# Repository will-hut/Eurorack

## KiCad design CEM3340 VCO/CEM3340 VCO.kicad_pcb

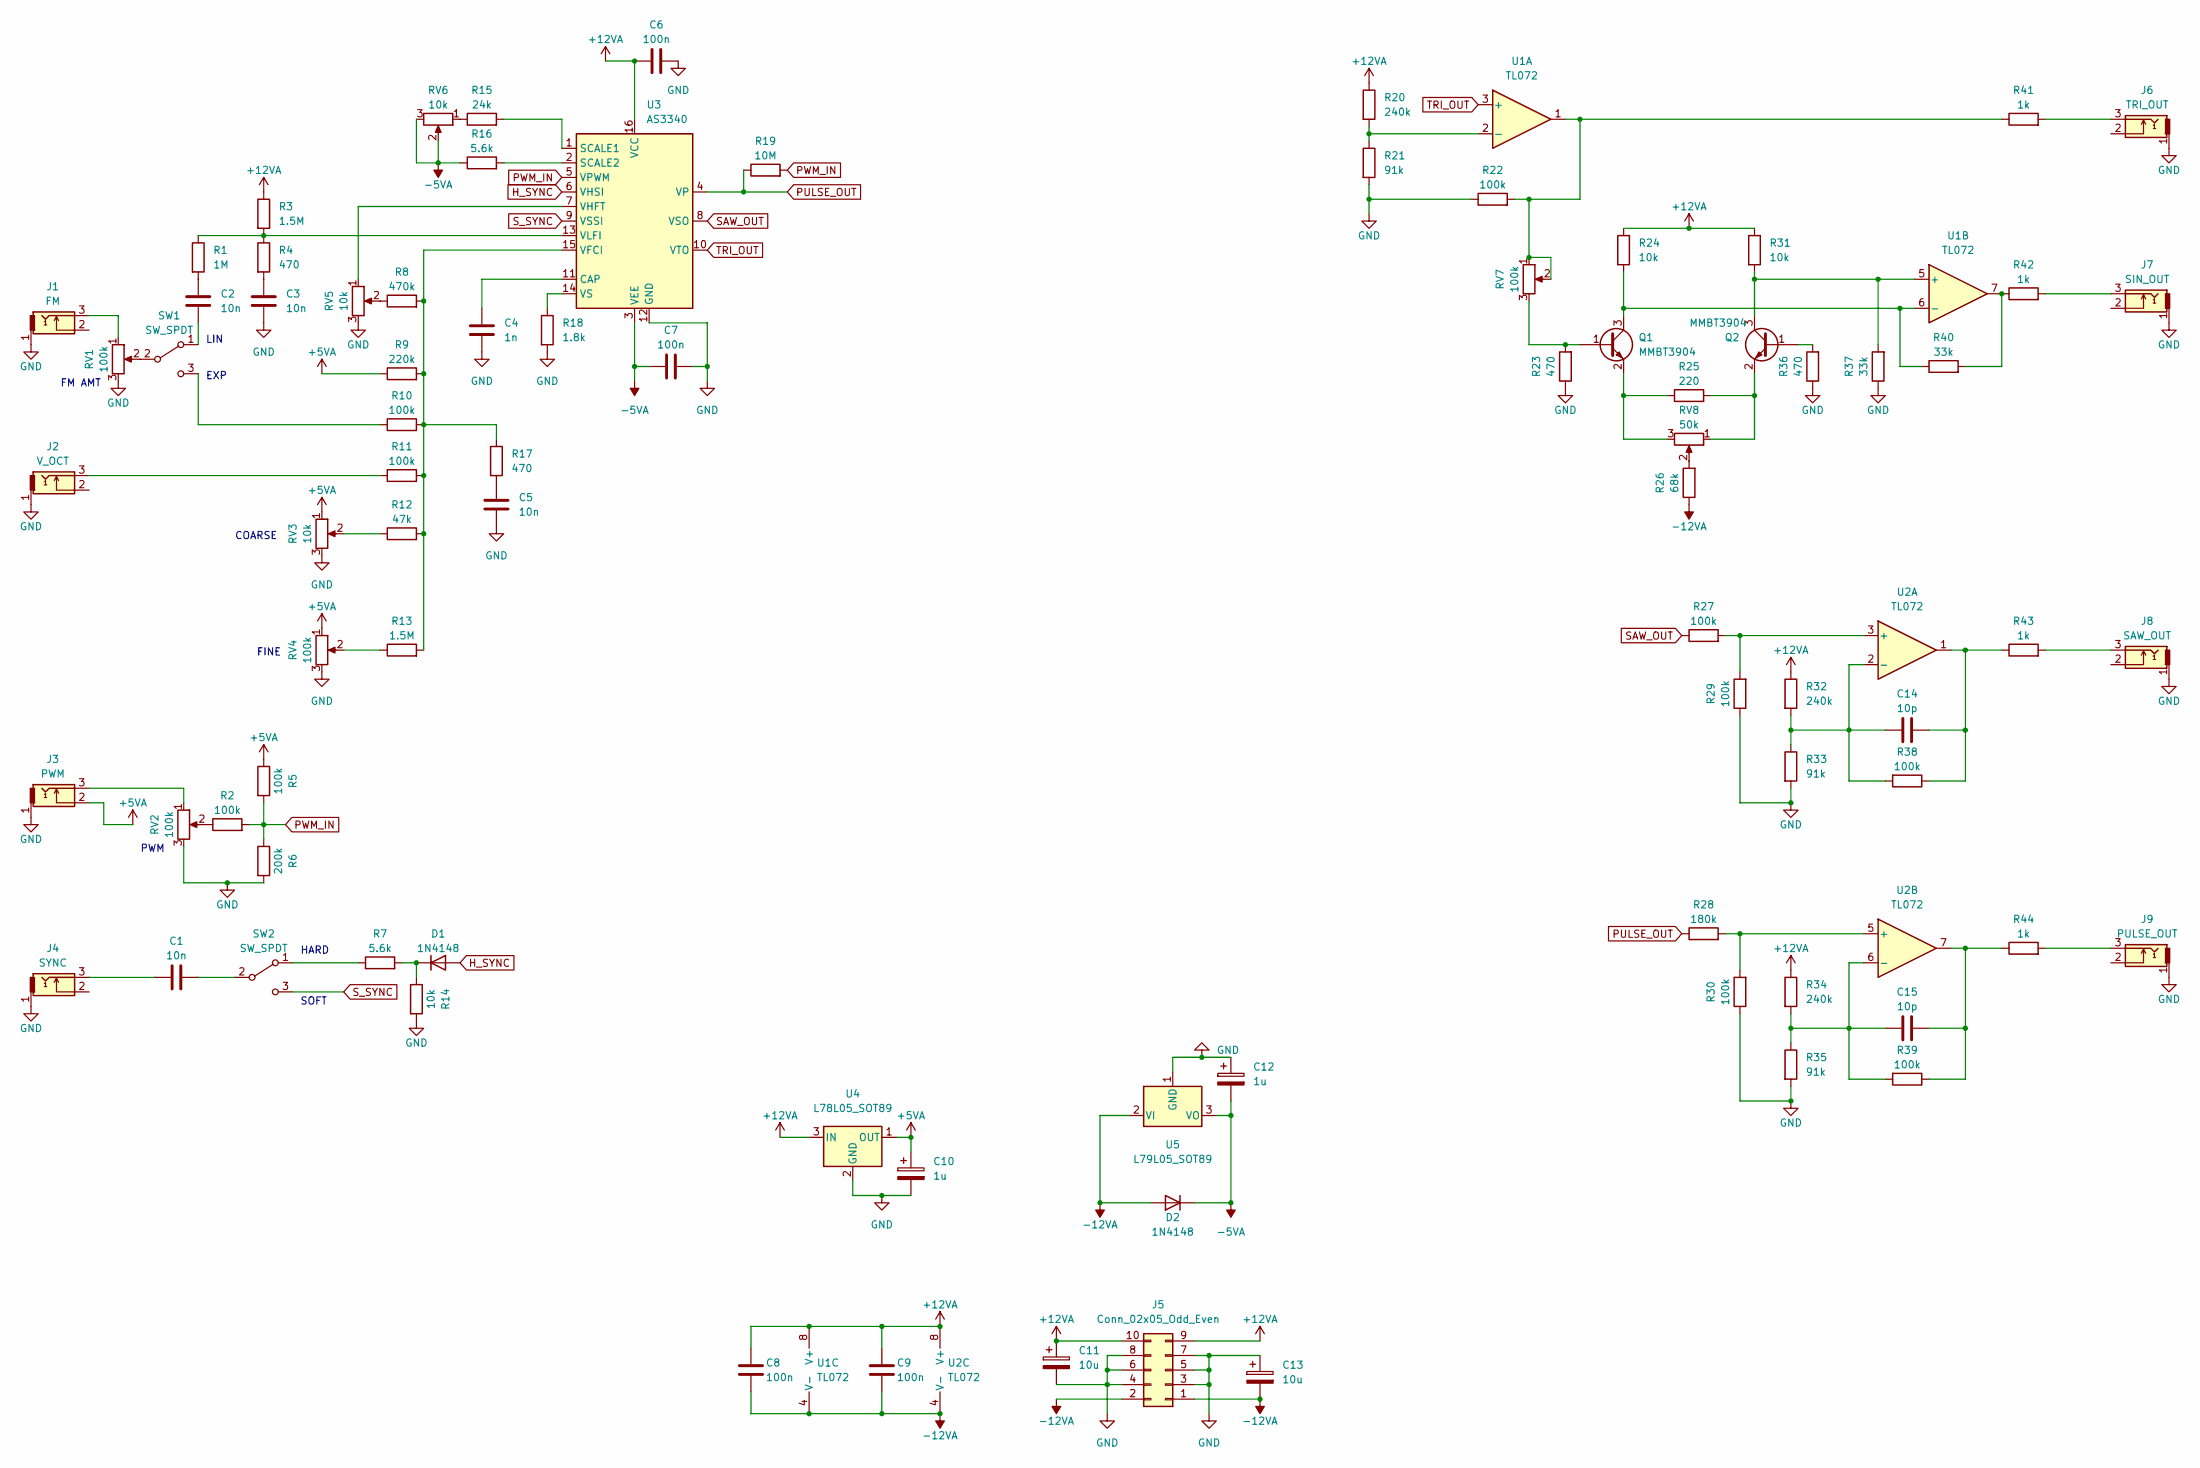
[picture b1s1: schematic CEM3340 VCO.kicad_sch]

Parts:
C1, C2, C3, C5: 10n; C_0603_1608Metric; LCSC C57112
C4: 1n; C_0603_1608Metric; LCSC C77026
C6, C7, C8, C9: 100n; C_0603_1608Metric; LCSC C14663
C10, C12: 1u; C_0603_1608Metric; LCSC C15849
C11, C13: 10u; CP_Radial_D6.3mm_P2.50mm
C14, C15: 10p; C_0603_1608Metric; LCSC C1634
D1, D2: 1N4148; D_SOD-123; LCSC C2128
J1: FM; thonkiconn
J2: V_OCT; thonkiconn
J3: PWM; thonkiconn
J4: SYNC; thonkiconn
J5: Conn_02x05_Odd_Even; PinHeader_2x05_P2.54mm_Vertical
J6: TRI_OUT; thonkiconn
J7: SIN_OUT; thonkiconn
J8: SAW_OUT; thonkiconn
J9: PULSE_OUT; thonkiconn
Q1, Q2: MMBT3904; SOT-23; LCSC C20526
R1: 1M; R_0603_1608Metric; LCSC C22935
R2, R5, R10, R11, R22, R27, R29, R30, R38, R39: 100k; R_0603_1608Metric; LCSC C25803
R3, R13: 1.5M; R_0603_1608Metric; LCSC C4172
R4, R17, R23, R36: 470; R_0603_1608Metric; LCSC C23179
R6: 200k; R_0603_1608Metric; LCSC C25811
R7, R16: 5.6k; R_0603_1608Metric; LCSC C23189
R8: 470k; R_0603_1608Metric; LCSC C23178
R9: 220k; R_0603_1608Metric; LCSC C22961
R12: 47k; R_0603_1608Metric; LCSC C25819
R14, R24, R31: 10k; R_0603_1608Metric; LCSC C25804
R15: 24k; R_0603_1608Metric; LCSC C23352
R18: 1.8k; R_0603_1608Metric; LCSC C4177
R19: 10M; R_0603_1608Metric; LCSC C7250
R20, R32, R34: 240k; R_0603_1608Metric; LCSC C4197
R21, R33, R35: 91k; R_0603_1608Metric; LCSC C23265
R25: 220; R_0603_1608Metric; LCSC C22962
R26: 68k; R_0603_1608Metric; LCSC C23231
R28: 180k; R_0603_1608Metric; LCSC C22827
R37, R40: 33k; R_0603_1608Metric; LCSC C4216
R41, R42, R43, R44: 1k; R_0603_1608Metric; LCSC C21190
RV1, RV2, RV4: 100k; alpha_rd901f
RV3: 10k; alpha_rd901f
RV5, RV6: 10k; Potentiometer_Bourns_3296W_Vertical
RV7: 100k; Potentiometer_Bourns_3296W_Vertical
RV8: 50k; Potentiometer_Bourns_3296W_Vertical
SW1, SW2: SW_SPDT; sw_dailywell_2M_M2
U1, U2: TL072; SOIC-8_3.9x4.9mm_P1.27mm; LCSC C6961
U3: AS3340; SO-16_3.9x9.9mm_P1.27mm
U4: L78L05_SOT89; SOT-89-3; LCSC C71136
U5: L79L05_SOT89; SOT-89-3; LCSC C157452

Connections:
+5VA: C10.1, J3.2, R5.1, R9.1, RV3.1, RV4.1, U4.1 (OUT)
+12VA: C6.1, C8.1, C9.1, C11.1, J5.9, J5.10, R3.1, R20.1, R24.1, R31.1, R32.1, R34.1, U1.8 (V+), U2.8 (V+), U3.16 (VCC), U4.3 (IN)
-5VA: C7.1, C12.2, D2.1 (K), R16.1, RV6.2, RV6.3, U3.3 (VEE), U5.3 (VO)
-12VA: C8.2, C9.2, C13.2, D2.2 (A), J5.1, J5.2, R26.1, U1.4 (V-), U2.4 (V-), U5.2 (VI)
GND: C3.2, C4.2, C5.2, C6.2, C7.2, C10.2, C11.2, C12.1, C13.1, J1.1, J2.1, J3.1, J4.1, J5.3, J5.4, J5.5, J5.6, J5.7, J5.8, J6.1, J7.1, J8.1, J9.1, R6.2, R14.2, R18.2, R21.2, R22.1, R23.1, R29.1, R30.1, R33.2, R35.2, R36.1, R37.1, RV1.3, RV2.3, RV3.3, RV4.3, RV5.3, U3.12 (GND), U4.2 (GND), U5.1 (GND)
H_SYNC: D1.2 (A), U3.6 (VHSI)
unnamed: C1.1, J4.3
unnamed: C1.2, SW2.2 (B)
unnamed: C2.1, R1.2
unnamed: C2.2, SW1.1 (A)
unnamed: C3.1, R4.2
unnamed: C4.1, U3.11 (CAP)
unnamed: C5.1, R17.2
unnamed: C14.1, R32.2, R33.1, R38.2, U2.2 (-)
unnamed: C14.2, R38.1, R43.1, U2.1
unnamed: C15.1, R34.2, R35.1, R39.2, U2.6 (-)
unnamed: C15.2, R39.1, R44.1, U2.7
unnamed: D1.1 (K), R7.2, R14.1
unnamed: J1.3, RV1.1
unnamed: J2.3, R11.1
unnamed: J3.3, RV2.1
unnamed: J6.3, R41.2
unnamed: J7.3, R42.2
unnamed: J8.3, R43.2
unnamed: J9.3, R44.2
unnamed: Q1.1 (B), R23.2, RV7.3
unnamed: Q1.2 (E), R25.1, RV8.3
unnamed: Q1.3 (C), R24.2, R40.1, U1.6 (-)
unnamed: Q2.1 (B), R36.2
unnamed: Q2.2 (E), R25.2, RV8.1
unnamed: Q2.3 (C), R31.2, R37.2, U1.5 (+)
unnamed: R1.1, R3.2, R4.1, U3.13 (VLFI)
unnamed: R2.1, RV2.2
unnamed: R7.1, SW2.1 (A)
unnamed: R8.1, RV5.2
unnamed: R10.1, SW1.3 (C)
unnamed: R8.2, R9.2, R10.2, R11.2, R12.2, R13.2, R17.1, U3.15 (VFCI)
unnamed: R12.1, RV3.2
unnamed: R13.1, RV4.2
unnamed: R15.1, RV6.1
unnamed: R15.2, U3.1 (SCALE1)
unnamed: R16.2, U3.2 (SCALE2)
unnamed: R18.1, U3.14 (VS)
unnamed: R20.2, R21.1, U1.2 (-)
unnamed: R22.2, R41.1, RV7.1, RV7.2, U1.1
unnamed: R26.2, RV8.2
unnamed: R27.2, R29.2, U2.3 (+)
unnamed: R28.2, R30.2, U2.5 (+)
unnamed: R40.2, R42.1, U1.7
unnamed: RV1.2, SW1.2 (B)
unnamed: RV5.1, U3.7 (VHFT)
PULSE_OUT: R19.1, R28.1, U3.4 (VP)
PWM_IN: R2.2, R5.2, R6.1, R19.2, U3.5 (VPWM)
SAW_OUT: R27.1, U3.8 (VSO)
S_SYNC: SW2.3 (C), U3.9 (VSSI)
TRI_OUT: U1.3 (+), U3.10 (VTO)

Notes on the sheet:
FINE
HARD
SOFT
PWM
COARSE
LIN
FM AMT
EXP

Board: 2 copper layers, 87 parts (1 on the bottom side), 56 nets, no tracks yet.

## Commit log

2023-01-08 intitial CEM3340 module planning
